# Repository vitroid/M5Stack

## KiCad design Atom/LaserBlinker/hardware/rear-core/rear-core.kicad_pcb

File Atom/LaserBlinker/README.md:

# LaserBlinker

前後分離のウインカー／ブレーキ連動。幹線は **12V + RS-485**。

## ビルド

```bash
pio run -e esp32-c3-supermini-front
pio run -e esp32-c3-supermini-rear
```

現行ファームは、市販モジュールで組んで実装まで済ませた試作向けで、前後とも **ESP32-C3 SuperMini**（`platformio.ini`）。ピン定義は `src/front/pins.h` / `src/rear/pins.h`。`hardware/*-core` は、その試作を JLCPCB の一枚基板にまとめ、トランシーバ・幹線コネクタ・MCU・拡張端子を変えた次の基板である。ファームはまだ基板側のピンへ追従していない。いきさつと対応表は `docs/pcb-layout-policy.md` の「いきさつ」。

## ハードウェア正本

| 役割 | 正本 | 備考 |
| --- | --- | --- |
| 後部 PCB・発注／配線 | **`hardware/rear-core/`** | `docs/rear-pcb-design.md`・`docs/rear-circuit.md` と対になる |
| 前部 PCB（JLCPCB 向け） | `hardware/front-core/` | MCU は **ESP32-S3-MINI-1**。現行 FW は C3 のまま |
| 前部プロト配線（実機） | `docs/front-circuit.md` | C3 SuperMini + GX12-4 + MAX485 |

`hardware/rear-core-claude/` は **非正本**（別生成のアーカイブ）。リポジトリには含めない（`.gitignore`）。手元に残っていても発注・配線の参照先にしないこと。

## ドキュメント

- `docs/pcb-layout-policy.md` — 試作から一体基板までのいきさつ、端子配置、動かさない条件（引き継ぎの入口）
- `PLAN.md` / `PLAN2.md` — それより前のメモ（M5Stack Core / Atom Lite、幹線 5V）。実機の結線ではない
- `docs/front-circuit.md` — 実装済み試作の前部結線（C3 SuperMini、GX12、MAX485）
- `docs/front-pcb-design.md` — 前部オールインワン PCB（S3）の回路定数とピン表
- `docs/rear-circuit.md` — 実装済み試作の後部結線
- `docs/rear-pcb-design.md` — 後部コア PCB（C3-MINI-1）の回路定数とピン表

## 幹線コネクタの注意

- プロト／`*-circuit.md`: **GX12-4**（1:12V, 2:GND, 3:A, 4:B）
- PCB 設計／`hardware/*-core`: **RJ45**（Passive PoE + A/B）

前後を混在させるときはアダプタかピン対応表が必要。

## Fab readiness（front-core）

JLCPCB 発注前ゲート。手はんだ作業はない。

| 項目 | 状態 |
| --- | --- |
| KiCad | **Yes** — `kicad-cli` **10.0.8**（`scripts/build_pcb.py`） |
| ERC | 0 |
| BOM/CPL | R21 / R22 / R3 収録済 |
| DRC unconnected | **3**（発注不可のまま） |
| rear-core | fab 完了・正本 |

残銅箔未接続（回路図ネットは存在。CH224K 移設後の配置密度で Freerouting 未解決）:

1. **R21** — `/VBUS_PD` → `U0` Pin8 `VBUS`
2. **R22** — `/VBUS_PD` → `U0` Pin1 `VDD`
3. **J3** CC1 (`A5`) → **R3** → GND

次は `R21`/`R22`/`R3` の再配置（または配線チャネル確保）→ DRC 0 → `fab/` 再出力。詳細は Project store `docs/laserblinker-front-wiring.md`。FW ピン追従は PCB 確定後。

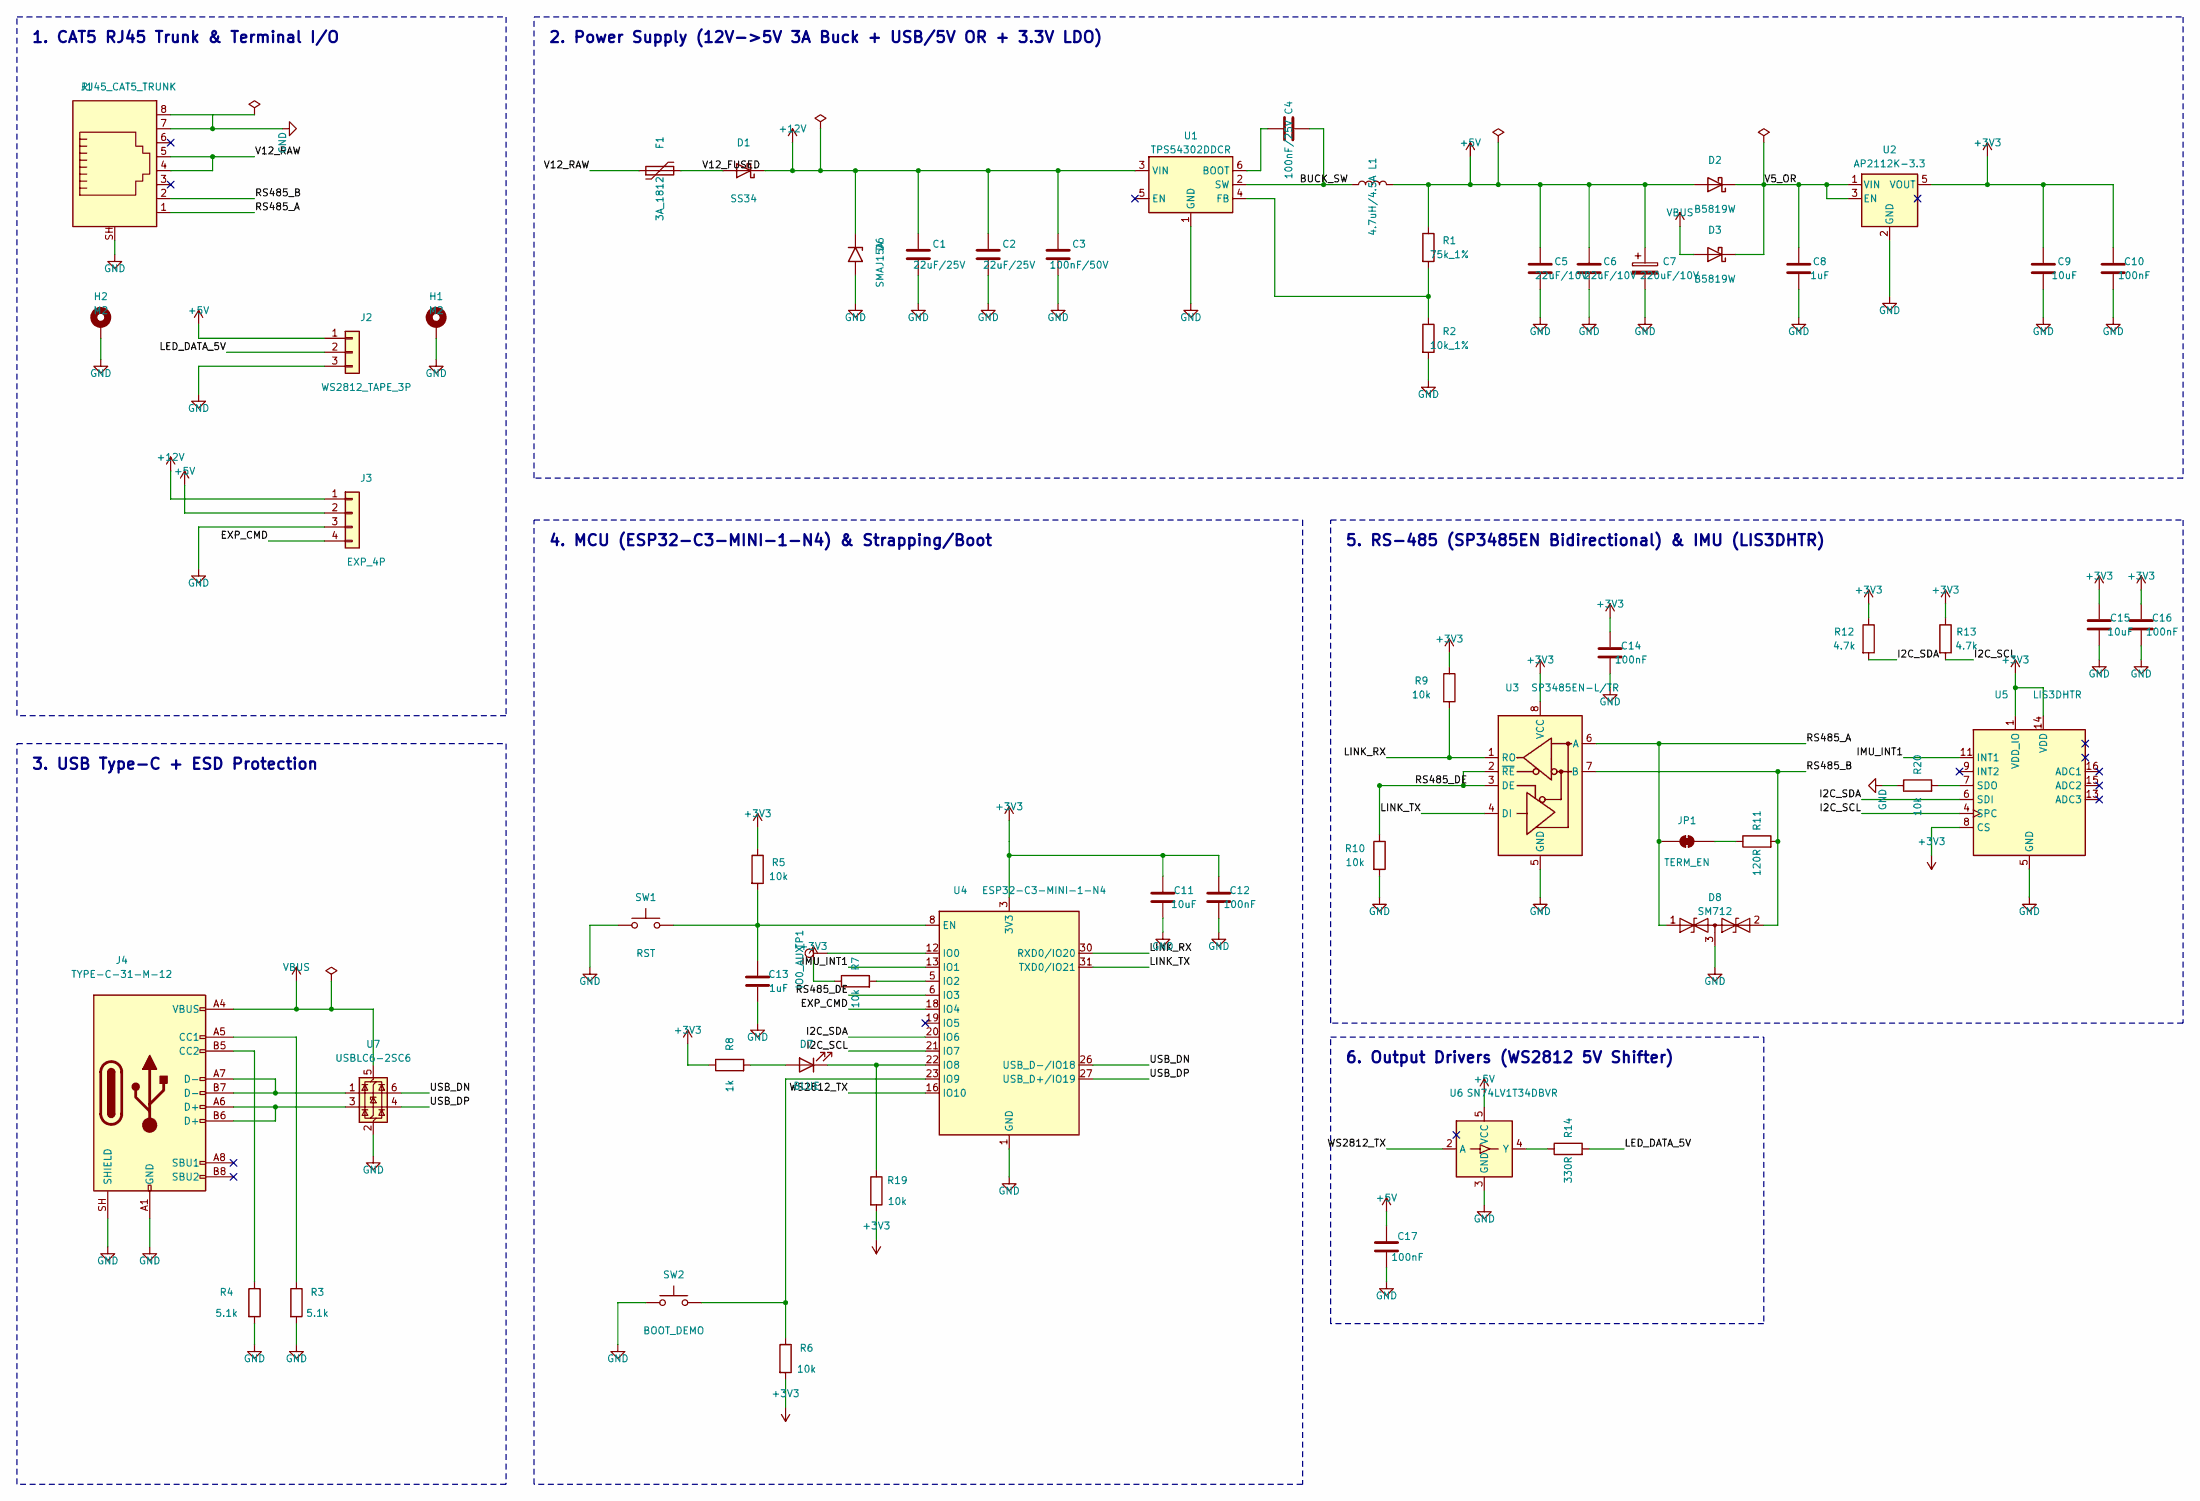
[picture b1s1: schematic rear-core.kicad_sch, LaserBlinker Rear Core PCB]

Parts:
C1, C2: 22uF/25V; C_1206_3216Metric; LCSC C12891
C3: 100nF/50V; C_0603_1608Metric; LCSC C14663
C4: 100nF/25V; C_0603_1608Metric; LCSC C14663
C5, C6: 22uF/10V; C_0805_2012Metric; LCSC C45783
C7: 220uF/10V; CP_Elec_6.3x7.7; LCSC C128268
C8, C13: 1uF; C_0603_1608Metric; LCSC C15849
C9, C11, C15: 10uF; C_0603_1608Metric; LCSC C19702
C10, C12, C14, C16, C17: 100nF; C_0603_1608Metric; LCSC C14663
D1: SS34; D_SMA; MPN SS34; LCSC C8678
D2, D3: B5819W; D_SOD-123; MPN B5819W; LCSC C8598
D6: SMAJ15A; D_SMA; MPN SMAJ15A; LCSC C123805
D7: BLUE; LED_0603_1608Metric; LCSC C72041
D8: SM712; SOT-23; MPN SM712; LCSC C15919
F1: 3A_1812; Fuse_1812_4532Metric; LCSC C70069
H1, H2: M2; MountingHole_2.2mm_M2_Pad_Via
J1: RJ45_CAT5_TRUNK; RJ45_Amphenol_RJHSE5380; MPN R-RJ45R08P-B000; LCSC C386756
J2: WS2812_TAPE_3P; JST_XH_S3B-XH-A_1x03_P2.50mm_Horizontal; MPN S3B-XH-A(LF)(SN); LCSC C157927
J3: EXP_4P; JST_XH_S4B-XH-A_1x04_P2.50mm_Horizontal; MPN S4B-XH-A(LF)(SN); LCSC C157928
J4: TYPE-C-31-M-12; USB_C_Receptacle_HRO_TYPE-C-31-M-12; MPN TYPE-C-31-M-12; LCSC C165948
JP1: TERM_EN; SolderJumper-2_P1.3mm_Bridged_RoundedPad1.0x1.5mm
L1: 4.7uH/4.5A; L_6.3x6.3_H3; LCSC C408412
R1: 75k_1%; R_0603_1608Metric; LCSC C23240
R2: 10k_1%; R_0603_1608Metric; LCSC C25804
R3, R4: 5.1k; R_0603_1608Metric; LCSC C23186
R5, R6, R7, R9, R10, R19, R20: 10k; R_0603_1608Metric; LCSC C25804
R8: 1k; R_0603_1608Metric; LCSC C21190
R11: 120R; R_0805_2012Metric; LCSC C17440
R12, R13: 4.7k; R_0603_1608Metric; LCSC C23162
R14: 330R; R_0603_1608Metric; LCSC C23138
SW1: RST; SW_Push_1P1T_XKB_TS-1187A; LCSC C318884
SW2: BOOT_DEMO; SW_Push_1P1T_XKB_TS-1187A; LCSC C318884
TP1: IO0_AUX; TestPoint_Pad_D1.5mm
U1: TPS54302DDCR; SOT-23-6; MPN TPS54302DDCR; LCSC C311038
U2: AP2112K-3.3; SOT-23-5; MPN AP2112K-3.3TRG1; LCSC C51118
U3: SP3485EN-L/TR; SOIC-8_3.9x4.9mm_P1.27mm; MPN SP3485EN-L/TR; LCSC C9945
U4: ESP32-C3-MINI-1-N4; ESP32-C3-MINI-1; MPN ESP32-C3-MINI-1-N4; LCSC C2838502
U5: LIS3DHTR; LGA-16_3x3mm_P0.5mm_LayoutBorder3x5y; MPN LIS3DHTR; LCSC C15134
U6: SN74LV1T34DBVR; SOT-23-5; MPN SN74LV1T34DBVR; LCSC C100022
U7: USBLC6-2SC6; SOT-23-6; MPN USBLC6-2SC6; LCSC C7519

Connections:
+3V3: C9.1, C10.1, C11.1, C12.1, C14.1, C15.1, C16.1, R5.1, R6.2, R7.1, R8.1, R9.1, R12.1, R13.1, R19.2, U2.5 (VOUT), U3.8 (VCC), U4.3 (3V3), U5.1 (VDD_IO), U5.8 (CS), U5.14 (VDD)
+5V: C5.1, C6.1, C7.1, C17.1, D2.2 (A), J2.1, J3.2, L1.2, R1.1, U6.5 (VCC)
+12V: C1.1, C2.1, C3.1, D1.1 (K), D6.1 (A1), J3.1, U1.3 (VIN)
/BUCK_SW: C4.2, L1.1, U1.2 (SW)
/EXP_CMD: J3.4, U4.18 (IO4)
/I2C_SCL: R13.2, U4.21 (IO7), U5.4 (SPC)
/I2C_SDA: R12.2, U4.20 (IO6), U5.6 (SDI)
/IMU_INT1: U4.13 (IO1), U5.11 (INT1)
/LED_DATA_5V: J2.2, R14.2
/LINK_RX: R9.2, U3.1 (RO), U4.30 (RXD0/IO20)
/LINK_TX: U3.4 (DI), U4.31 (TXD0/IO21)
/RS485_A: D8.1 (A1), J1.1, JP1.1 (A), U3.6 (A)
/RS485_B: D8.2 (A2), J1.2, R11.2, U3.7 (B)
/RS485_DE: R10.1, U3.2 (~RE), U3.3 (DE), U4.6 (IO3)
/USB_DN: U4.26 (USB_D-/IO18), U7.6 (I/O1)
/USB_DP: U4.27 (USB_D+/IO19), U7.4 (I/O2)
/V5_OR: C8.1, D2.1 (K), D3.1 (K), U2.1 (VIN), U2.3 (EN)
/V12_FUSED: D1.2 (A), F1.2
/V12_RAW: F1.1, J1.4, J1.5
/WS2812_TX: U4.16 (IO10), U6.2 (A)
GND: C1.2, C2.2, C3.2, C5.2, C6.2, C7.2, C8.2, C9.2, C10.2, C11.2, C12.2, C13.2, C14.2, C15.2, C16.2, C17.2, D6.2 (A2), D8.3 (common), H1.1, H2.1, J1.7, J1.8, J1.SH, J2.3, J3.3, J4.A1 (GND), J4.A12 (GND), J4.B1 (GND), J4.B12 (GND), J4.SH (SHIELD), R2.2, R3.2, R4.2, R10.2, R20.1, SW1.1, SW2.1, U1.1 (GND), U2.2 (GND), U3.5 (GND), U4.1 (GND), U4.2 (GND), U4.11 (GND), U4.14 (GND), U4.36 (GND), U4.37 (GND), U4.38 (GND), U4.39 (GND), U4.40 (GND), U4.41 (GND), U4.42 (GND), U4.43 (GND), U4.44 (GND), U4.45 (GND), U4.46 (GND), U4.47 (GND), U4.48 (GND), U4.49 (GND), U4.50 (GND), U4.51 (GND), U4.52 (GND), U4.53 (GND), U5.5 (GND), U5.10 (GND), U5.12 (GND), U6.3 (GND), U7.2 (GND)
unnamed: D7.2 (A), R8.2
unnamed: D7.1 (K), R19.1, U4.22 (IO8)
unnamed: J4.A5 (CC1), R3.1
unnamed: J4.B5 (CC2), R4.1
unnamed: J4.A6 (D+), J4.B6 (D+), U7.3 (I/O2)
unnamed: J4.A7 (D-), J4.B7 (D-), U7.1 (I/O1)
unnamed: JP1.2 (B), R11.1
unnamed: C4.1, U1.6 (BOOT)
unnamed: R1.2, R2.1, U1.4 (FB)
unnamed: C13.1, R5.2, SW1.2, U4.8 (EN)
unnamed: TP1.1, U4.12 (IO0)
unnamed: R7.2, U4.5 (IO2)
unnamed: R6.1, SW2.2, U4.23 (IO9)
unnamed: R20.2, U5.7 (SDO)
unnamed: R14.1, U6.4 (Y)
VBUS: D3.2 (A), J4.A4 (VBUS), J4.A9 (VBUS), J4.B4 (VBUS), J4.B9 (VBUS), U7.5 (VBUS)

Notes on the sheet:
1. CAT5 RJ45 Trunk & Terminal I/O
2. Power Supply (12V->5V 3A Buck + USB/5V OR + 3.3V LDO)
3. USB Type-C + ESD Protection
4. MCU (ESP32-C3-MINI-1-N4) & Strapping/Boot
5. RS-485 (SP3485EN Bidirectional) & IMU (LIS3DHTR)
6. Output Drivers (WS2812 5V Shifter)

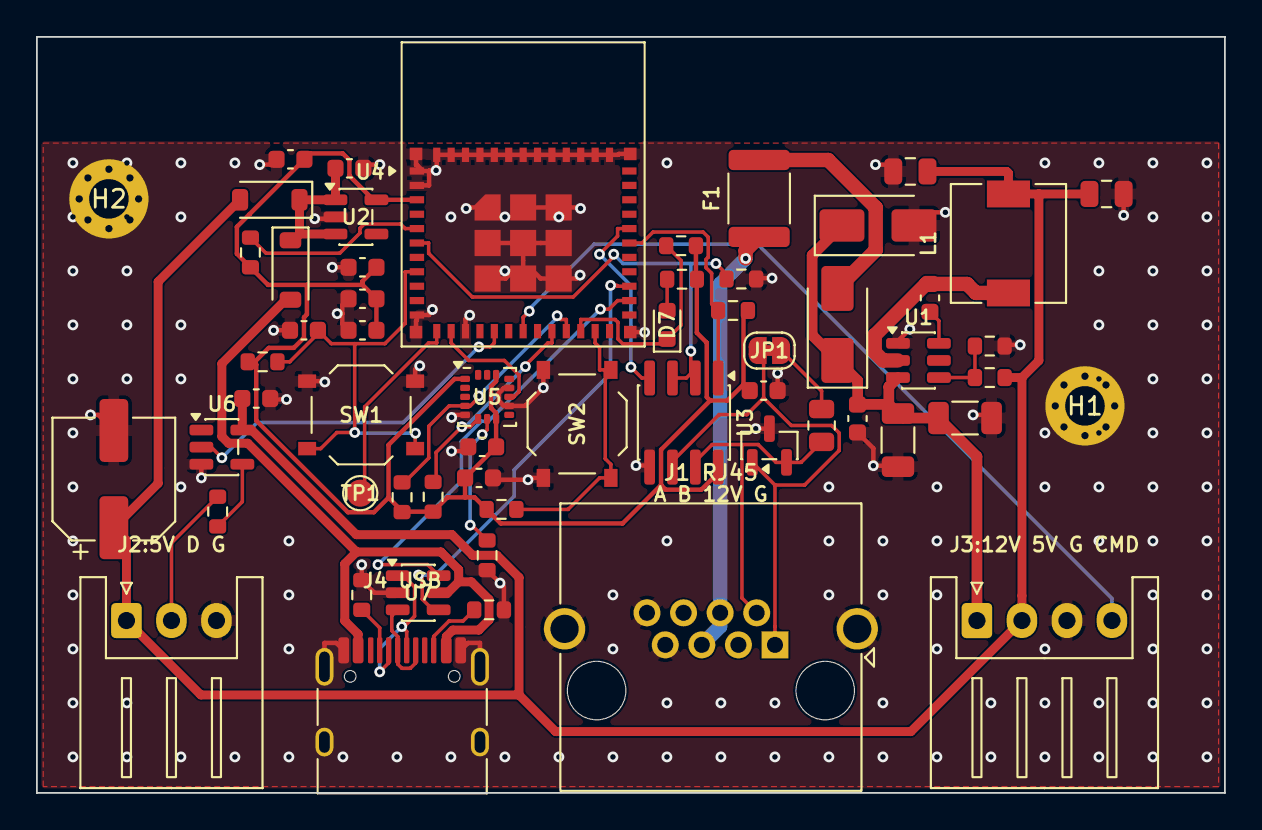
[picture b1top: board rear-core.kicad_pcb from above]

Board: 2 copper layers, 66.0 x 42.0 mm, 58 parts (0 on the bottom side), 37 nets.

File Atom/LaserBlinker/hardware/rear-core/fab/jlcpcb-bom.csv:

"Comment","Designator","Footprint","JLCPCB Part #"
"22uF/25V","C1,C2","Capacitor_SMD:C_1206_3216Metric","C12891"
"100nF/50V","C3","Capacitor_SMD:C_0603_1608Metric","C14663"
"100nF/25V","C4","Capacitor_SMD:C_0603_1608Metric","C14663"
"22uF/10V","C5,C6","Capacitor_SMD:C_0805_2012Metric","C45783"
"220uF/10V","C7","Capacitor_SMD:CP_Elec_6.3x7.7","C128268"
"1uF","C8,C13","Capacitor_SMD:C_0603_1608Metric","C15849"
"10uF","C9,C11,C15","Capacitor_SMD:C_0603_1608Metric","C19702"
"100nF","C10,C12,C14,C16,C17","Capacitor_SMD:C_0603_1608Metric","C14663"
"SS34","D1","Diode_SMD:D_SMA","C8678"
"B5819W","D2,D3","Diode_SMD:D_SOD-123","C8598"
"SMAJ15A","D6","Diode_SMD:D_SMA","C123805"
"BLUE","D7","LED_SMD:LED_0603_1608Metric","C72041"
"SM712","D8","Package_TO_SOT_SMD:SOT-23","C15919"
"3A_1812","F1","Fuse:Fuse_1812_4532Metric","C70069"
"RJ45_CAT5_TRUNK","J1","Connector_RJ:RJ45_Amphenol_RJHSE5380","C386756"
"WS2812_TAPE_3P","J2","Connector_JST:JST_XH_S3B-XH-A_1x03_P2.50mm_Horizontal","C157927"
"EXP_4P","J3","Connector_JST:JST_XH_S4B-XH-A_1x04_P2.50mm_Horizontal","C157928"
"TYPE-C-31-M-12","J4","Connector_USB:USB_C_Receptacle_HRO_TYPE-C-31-M-12","C165948"
"4.7uH/4.5A","L1","Inductor_SMD:L_6.3x6.3_H3","C408412"
"75k_1%","R1","Resistor_SMD:R_0603_1608Metric","C23240"
"10k_1%","R2","Resistor_SMD:R_0603_1608Metric","C25804"
"5.1k","R3,R4","Resistor_SMD:R_0603_1608Metric","C23186"
"10k","R5,R6,R7,R9,R10,R19,R20","Resistor_SMD:R_0603_1608Metric","C25804"
"1k","R8","Resistor_SMD:R_0603_1608Metric","C21190"
"120R","R11","Resistor_SMD:R_0805_2012Metric","C17440"
"4.7k","R12,R13","Resistor_SMD:R_0603_1608Metric","C23162"
"330R","R14","Resistor_SMD:R_0603_1608Metric","C23138"
"RST","SW1","Button_Switch_SMD:SW_Push_1P1T_XKB_TS-1187A","C318884"
"BOOT_DEMO","SW2","Button_Switch_SMD:SW_Push_1P1T_XKB_TS-1187A","C318884"
"TPS54302DDCR","U1","Package_TO_SOT_SMD:SOT-23-6","C311038"
"AP2112K-3.3","U2","Package_TO_SOT_SMD:SOT-23-5","C51118"
"SP3485EN-L/TR","U3","Package_SO:SOIC-8_3.9x4.9mm_P1.27mm","C9945"
"ESP32-C3-MINI-1-N4","U4","RearCore:ESP32-C3-MINI-1","C2838502"
"LIS3DHTR","U5","Package_LGA:LGA-16_3x3mm_P0.5mm_LayoutBorder3x5y","C15134"
"SN74LV1T34DBVR","U6","Package_TO_SOT_SMD:SOT-23-5","C100022"
"USBLC6-2SC6","U7","Package_TO_SOT_SMD:SOT-23-6","C7519"

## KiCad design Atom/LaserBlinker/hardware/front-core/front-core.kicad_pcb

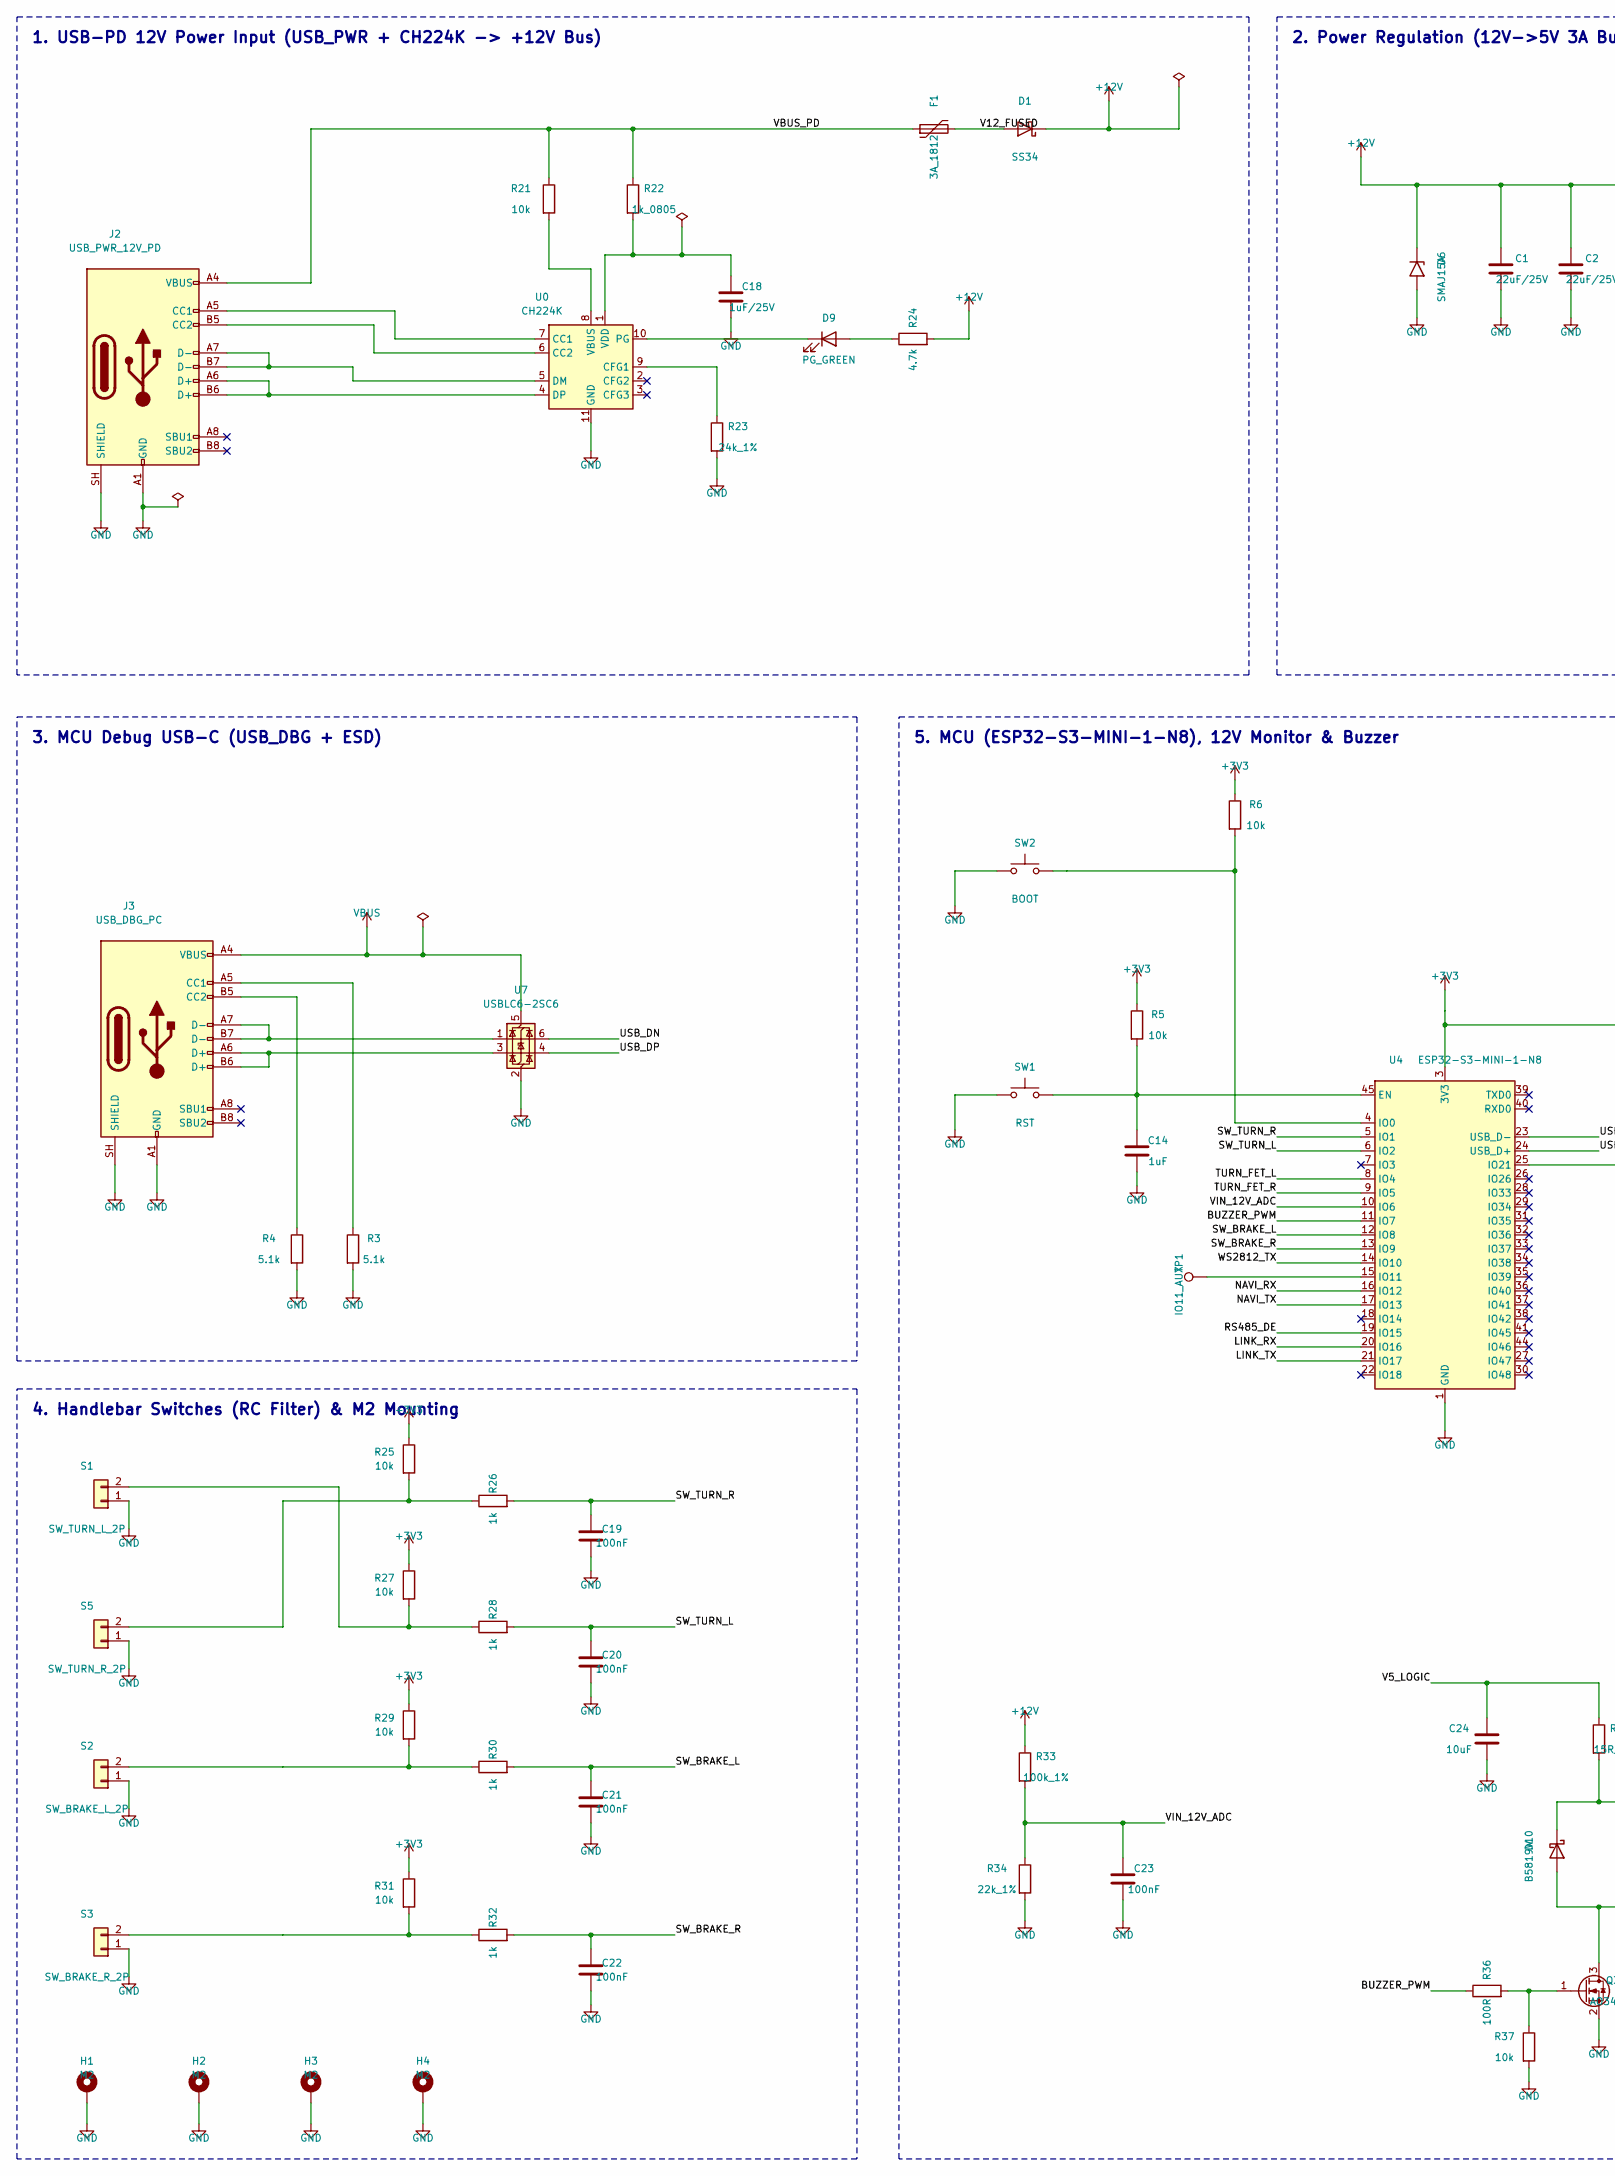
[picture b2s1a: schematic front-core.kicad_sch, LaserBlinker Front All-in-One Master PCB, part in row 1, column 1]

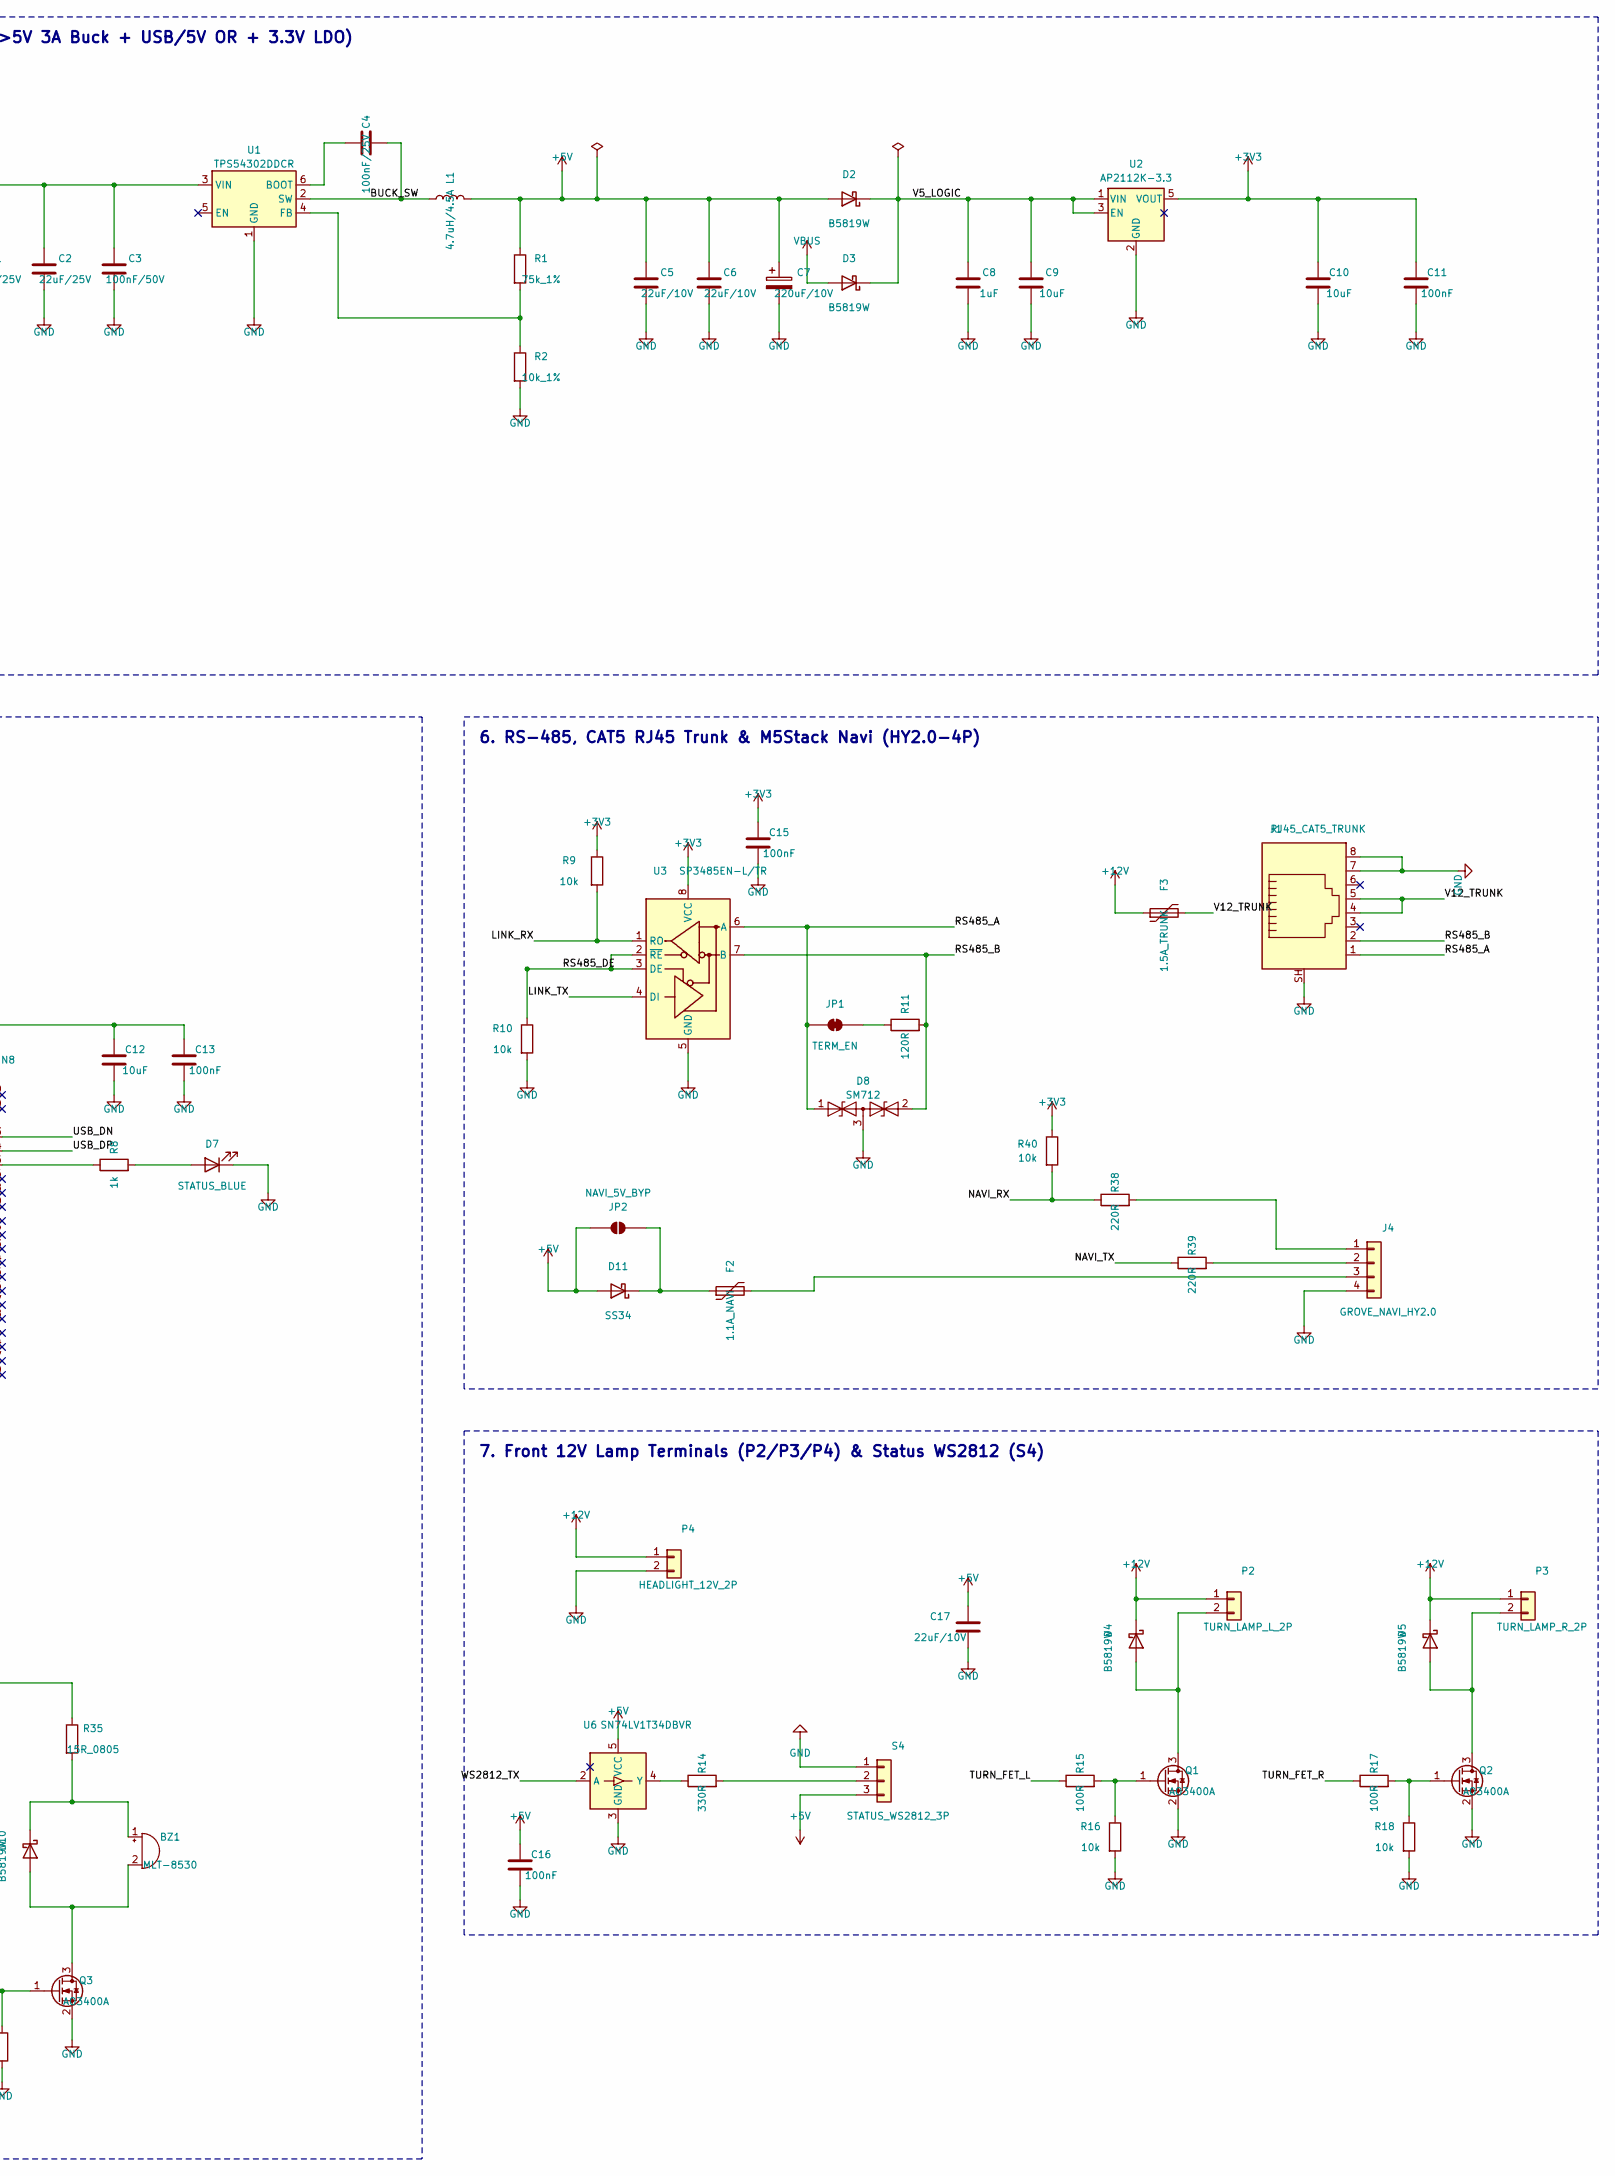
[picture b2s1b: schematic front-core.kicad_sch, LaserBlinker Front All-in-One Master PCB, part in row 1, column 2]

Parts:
BZ1: MLT-8530; MagneticBuzzer_CUI_CMT-8504-100-SMT; MPN MLT-8530; LCSC C94599
C1, C2: 22uF/25V; C_1206_3216Metric; LCSC C12891
C3: 100nF/50V; C_0603_1608Metric; LCSC C14663
C4: 100nF/25V; C_0603_1608Metric; LCSC C14663
C5, C6, C17: 22uF/10V; C_0805_2012Metric; LCSC C45783
C7: 220uF/10V; CP_Elec_6.3x7.7; LCSC C128268
C8, C14: 1uF; C_0603_1608Metric; LCSC C15849
C9, C10, C12, C24: 10uF; C_0603_1608Metric; LCSC C19702
C11, C13, C15, C16, C19, C20, C21, C22, C23: 100nF; C_0603_1608Metric; LCSC C14663
C18: 1uF/25V; C_0603_1608Metric; LCSC C15849
D1, D11: SS34; D_SMA; MPN SS34; LCSC C8678
D2, D3, D4, D5, D10: B5819W; D_SOD-123; MPN B5819W; LCSC C8598
D6: SMAJ15A; D_SMA; MPN SMAJ15A; LCSC C123805
D7: STATUS_BLUE; LED_0603_1608Metric; LCSC C72041
D8: SM712; SOT-23; MPN SM712; LCSC C15919
D9: PG_GREEN; LED_0603_1608Metric; LCSC C72043
F1: 3A_1812; Fuse_1812_4532Metric; LCSC C70069
F2: 1.1A_NAVI; Fuse_1206_3216Metric; LCSC C70059
F3: 1.5A_TRUNK; Fuse_1206_3216Metric; LCSC C70062
H1, H2, H3, H4: M2; MountingHole_2.2mm_M2_Pad_Via
J1: RJ45_CAT5_TRUNK; RJ45_Amphenol_RJHSE5380; MPN R-RJ45R08P-C000; LCSC C386757
J2: USB_PWR_12V_PD; USB_C_Receptacle_HRO_TYPE-C-31-M-12; MPN TYPE-C-31-M-12; LCSC C165948
J3: USB_DBG_PC; USB_C_Receptacle_HRO_TYPE-C-31-M-12; MPN TYPE-C-31-M-12; LCSC C165948
J4: GROVE_NAVI_HY2.0; JST_PH_S4B-PH-K_1x04_P2.00mm_Horizontal; MPN S4B-PH-K(LF)(SN); LCSC C265452
JP1: TERM_EN; SolderJumper-2_P1.3mm_Bridged_RoundedPad1.0x1.5mm
JP2: NAVI_5V_BYP; SolderJumper-2_P1.3mm_Open_RoundedPad1.0x1.5mm
L1: 4.7uH/4.5A; L_6.3x6.3_H3; LCSC C408412
P2: TURN_LAMP_L_2P; TerminalBlock_4Ucon_1x02_P3.50mm_Horizontal; MPN KF350-3.5-2P; LCSC C474892
P3: TURN_LAMP_R_2P; TerminalBlock_4Ucon_1x02_P3.50mm_Horizontal; MPN KF350-3.5-2P; LCSC C474892
P4: HEADLIGHT_12V_2P; TerminalBlock_4Ucon_1x02_P3.50mm_Horizontal; MPN KF350-3.5-2P; LCSC C474892
Q1, Q2, Q3: AO3400A; SOT-23; MPN AO3400A; LCSC C20917
R1: 75k_1%; R_0603_1608Metric; LCSC C23240
R2: 10k_1%; R_0603_1608Metric; LCSC C25804
R3, R4: 5.1k; R_0603_1608Metric; LCSC C23186
R5, R6, R9, R10, R16, R18, R21, R25, R27, R29, R31, R37, R40: 10k; R_0603_1608Metric; LCSC C25804
R8, R26, R28, R30, R32: 1k; R_0603_1608Metric; LCSC C21190
R11: 120R; R_0805_2012Metric; LCSC C17440
R14: 330R; R_0603_1608Metric; LCSC C23138
R15, R17, R36: 100R; R_0603_1608Metric; LCSC C22775
R22: 1k_0805; R_0805_2012Metric; LCSC C17513
R23: 24k_1%; R_0603_1608Metric; LCSC C23350
R24: 4.7k; R_0603_1608Metric; LCSC C23162
R33: 100k_1%; R_0603_1608Metric; LCSC C25803
R34: 22k_1%; R_0603_1608Metric; LCSC C25768
R35: 15R_0805; R_0805_2012Metric; LCSC C17471
R38, R39: 220R; R_0603_1608Metric; LCSC C22962
S1: SW_TURN_L_2P; TerminalBlock_Xinya_XY308-2.54-2P_1x02_P2.54mm_Horizontal; MPN XY308-2.54-2P; LCSC C557685
S2: SW_BRAKE_L_2P; TerminalBlock_Xinya_XY308-2.54-2P_1x02_P2.54mm_Horizontal; MPN XY308-2.54-2P; LCSC C557685
S3: SW_BRAKE_R_2P; TerminalBlock_Xinya_XY308-2.54-2P_1x02_P2.54mm_Horizontal; MPN XY308-2.54-2P; LCSC C557685
S4: STATUS_WS2812_3P; TerminalBlock_Xinya_XY308-2.54-3P_1x03_P2.54mm_Horizontal; MPN XY308-2.54-3P; LCSC C557686
S5: SW_TURN_R_2P; TerminalBlock_Xinya_XY308-2.54-2P_1x02_P2.54mm_Horizontal; MPN XY308-2.54-2P; LCSC C557685
SW1: RST; SW_Push_1P1T_XKB_TS-1187A; LCSC C318884
SW2: BOOT; SW_Push_1P1T_XKB_TS-1187A; LCSC C318884
TP1: IO11_AUX; TestPoint_Pad_D1.5mm
U0: CH224K; SSOP-10-1EP_3.9x4.9mm_P1mm_EP2.1x3.3mm; MPN CH224K; LCSC C970725
U1: TPS54302DDCR; SOT-23-6; MPN TPS54302DDCR; LCSC C311038
U2: AP2112K-3.3; SOT-23-5; MPN AP2112K-3.3TRG1; LCSC C51118
U3: SP3485EN-L/TR; SOIC-8_3.9x4.9mm_P1.27mm; MPN SP3485EN-L/TR; LCSC C9945
U4: ESP32-S3-MINI-1-N8; ESP32-S2-MINI-1; MPN ESP32-S3-MINI-1-N8; LCSC C2913206
U6: SN74LV1T34DBVR; SOT-23-5; MPN SN74LV1T34DBVR; LCSC C100022
U7: USBLC6-2SC6; SOT-23-6; MPN USBLC6-2SC6; LCSC C7519

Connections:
+3V3: C10.1, C11.1, C12.1, C13.1, C15.1, R5.1, R6.1, R9.1, R25.1, R27.1, R29.1, R31.1, R40.1, U2.5 (VOUT), U3.8 (VCC), U4.3 (3V3)
+5V: C5.1, C6.1, C7.1, C16.1, C17.1, D2.2 (A), D11.2 (A), JP2.1 (A), L1.2, R1.1, S4.3, U6.5 (VCC)
+12V: C1.1, C2.1, C3.1, D1.1 (K), D4.1 (K), D5.1 (K), D6.1 (A1), F3.1, P2.1, P3.1, P4.1, R24.2, R33.1, U1.3 (VIN)
/BUCK_SW: C4.2, L1.1, U1.2 (SW)
/BUZZER_PWM: R36.1, U4.11 (IO7)
/LINK_RX: R9.2, U3.1 (RO), U4.20 (IO16)
/LINK_TX: U3.4 (DI), U4.21 (IO17)
/NAVI_RX: R38.1, R40.2, U4.16 (IO12)
/NAVI_TX: R39.1, U4.17 (IO13)
/RS485_A: D8.1 (A1), J1.1, JP1.1 (A), U3.6 (A)
/RS485_B: D8.2 (A2), J1.2, R11.2, U3.7 (B)
/RS485_DE: R10.1, U3.2 (~RE), U3.3 (DE), U4.19 (IO15)
/SW_BRAKE_L: C21.1, R30.2, U4.12 (IO8)
/SW_BRAKE_R: C22.1, R32.2, U4.13 (IO9)
/SW_TURN_L: C20.1, R28.2, U4.6 (IO2)
/SW_TURN_R: C19.1, R26.2, U4.5 (IO1)
/TURN_FET_L: R15.1, U4.8 (IO4)
/TURN_FET_R: R17.1, U4.9 (IO5)
/USB_DN: U4.23 (USB_D-), U7.6 (I/O1)
/USB_DP: U4.24 (USB_D+), U7.4 (I/O2)
/V5_LOGIC: C8.1, C9.1, C24.1, D2.1 (K), D3.1 (K), R35.1, U2.1 (VIN), U2.3 (EN)
/V12_FUSED: D1.2 (A), F1.2
/V12_TRUNK: F3.2, J1.4, J1.5
/VBUS_PD: F1.1, J2.A4 (VBUS), J2.A9 (VBUS), J2.B4 (VBUS), J2.B9 (VBUS), R21.1, R22.1
/VIN_12V_ADC: C23.1, R33.2, R34.1, U4.10 (IO6)
/WS2812_TX: U4.14 (IO10), U6.2 (A)
GND: C1.2, C2.2, C3.2, C5.2, C6.2, C7.2, C8.2, C9.2, C10.2, C11.2, C12.2, C13.2, C14.2, C15.2, C16.2, C17.2, C18.2, C19.2, C20.2, C21.2, C22.2, C23.2, C24.2, D6.2 (A2), D7.1 (K), D8.3 (common), H1.1, H2.1, H3.1, H4.1, J1.7, J1.8, J1.SH, J2.A1 (GND), J2.A12 (GND), J2.B1 (GND), J2.B12 (GND), J2.SH (SHIELD), J3.A1 (GND), J3.A12 (GND), J3.B1 (GND), J3.B12 (GND), J3.SH (SHIELD), J4.4, P4.2, Q1.2 (S), Q2.2 (S), Q3.2 (S), R2.2, R3.2, R4.2, R10.2, R16.2, R18.2, R23.2, R34.2, R37.2, S1.1, S2.1, S3.1, S4.1, S5.1, SW1.1, SW2.1, U0.11 (GND), U1.1 (GND), U2.2 (GND), U3.5 (GND), U4.1 (GND), U4.2 (GND), U4.42 (GND), U4.43 (GND), U4.46 (GND), U4.47 (GND), U4.48 (GND), U4.49 (GND), U4.50 (GND), U4.51 (GND), U4.52 (GND), U4.53 (GND), U4.54 (GND), U4.55 (GND), U4.56 (GND), U4.57 (GND), U4.58 (GND), U4.59 (GND), U4.60 (GND), U4.61 (GND), U4.62 (GND), U4.63 (GND), U4.64 (GND), U4.65 (GND), U6.3 (GND), U7.2 (GND)
unnamed: BZ1.1 (+), D10.1 (K), R35.2
unnamed: BZ1.2 (-), D10.2 (A), Q3.3 (D)
unnamed: D4.2 (A), P2.2, Q1.3 (D)
unnamed: D5.2 (A), P3.2, Q2.3 (D)
unnamed: D7.2 (A), R8.2
unnamed: D9.2 (A), R24.1
unnamed: D9.1 (K), U0.10 (PG)
unnamed: D11.1 (K), F2.1, JP2.2 (B)
unnamed: J2.A5 (CC1), U0.7 (CC1)
unnamed: J2.B5 (CC2), U0.6 (CC2)
unnamed: J3.A5 (CC1), R3.1
unnamed: J3.B5 (CC2), R4.1
unnamed: J3.A6 (D+), J3.B6 (D+), U7.3 (I/O2)
unnamed: J3.A7 (D-), J3.B7 (D-), U7.1 (I/O1)
unnamed: J4.1, R38.2
unnamed: J4.2, R39.2
unnamed: F2.2, J4.3
unnamed: JP1.2 (B), R11.1
unnamed: Q1.1 (G), R15.2, R16.1
unnamed: Q2.1 (G), R17.2, R18.1
unnamed: Q3.1 (G), R36.2, R37.1
unnamed: R27.2, R28.1, S1.2
unnamed: R29.2, R30.1, S2.2
unnamed: R31.2, R32.1, S3.2
unnamed: R14.2, S4.2
unnamed: R25.2, R26.1, S5.2
unnamed: R23.1, U0.9 (CFG1)
unnamed: J2.A7 (D-), J2.B7 (D-), U0.5 (DM)
unnamed: J2.A6 (D+), J2.B6 (D+), U0.4 (DP)
unnamed: R21.2, U0.8 (VBUS)
unnamed: C18.1, R22.2, U0.1 (VDD)
unnamed: C4.1, U1.6 (BOOT)
unnamed: R1.2, R2.1, U1.4 (FB)
unnamed: C14.1, R5.2, SW1.2, U4.45 (EN)
unnamed: R6.2, SW2.2, U4.4 (IO0)
unnamed: TP1.1, U4.15 (IO11)
unnamed: R8.1, U4.25 (IO21)
unnamed: R14.1, U6.4 (Y)
VBUS: D3.2 (A), J3.A4 (VBUS), J3.A9 (VBUS), J3.B4 (VBUS), J3.B9 (VBUS), U7.5 (VBUS)

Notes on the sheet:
1. USB-PD 12V Power Input (USB_PWR + CH224K -> +12V Bus)
2. Power Regulation (12V->5V 3A Buck + USB/5V OR + 3.3V LDO)
3. MCU Debug USB-C (USB_DBG + ESD)
4. Handlebar Switches (RC Filter) & M2 Mounting
5. MCU (ESP32-S3-MINI-1-N8), 12V Monitor & Buzzer
6. RS-485, CAT5 RJ45 Trunk & M5Stack Navi (HY2.0-4P)
7. Front 12V Lamp Terminals (P2/P3/P4) & Status WS2812 (S4)
